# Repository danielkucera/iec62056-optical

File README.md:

# iec62056-optical

Adapter for reading meters with IEC62056 optical interface.

View this project [online](https://kicanvas.org/?github=https%3A%2F%2Fgithub.com%2Fdanielkucera%2Fiec62056-optical%2Ftree%2Fmaster)

You can buy complete adapter in [my shop](https://lectronz.com/products/iec-62056-optical-interface)

# Photos

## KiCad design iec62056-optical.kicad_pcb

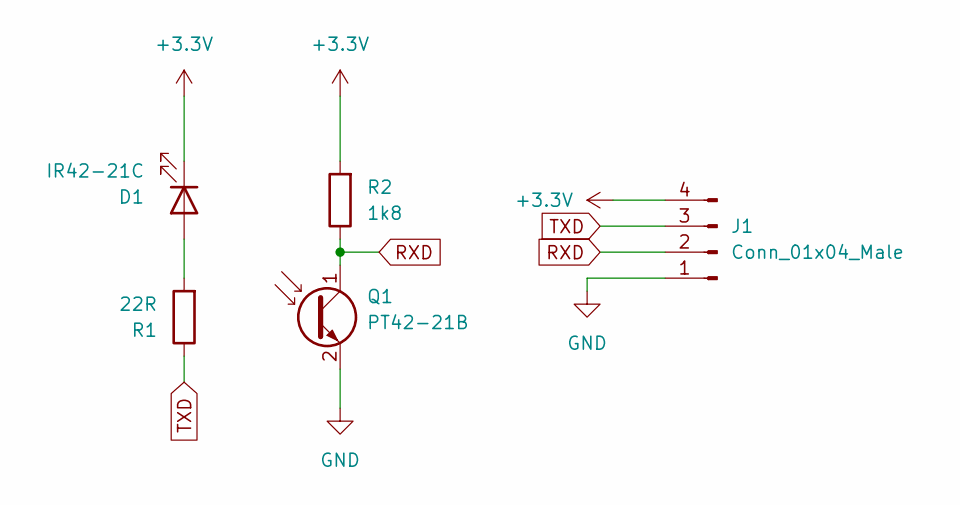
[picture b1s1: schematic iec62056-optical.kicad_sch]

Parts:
D1: IR42-21C; LED_1210_3225Metric; LCSC C131198
J1: Conn_01x04_Male; PinHeader_1x04_P2.54mm_Vertical
Q1: PT42-21B; LED_1210_3225Metric; LCSC C131199
R1: 22R; R_0603_1608Metric; LCSC C23345
R2: 1k8; R_0603_1608Metric; LCSC C4177

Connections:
+3V3: D1.1 (K), J1.4, R2.2
GND: J1.1, Q1.2 (E)
unnamed: D1.2 (A), R1.2
RXD: J1.2, Q1.1 (C), R2.1
TXD: J1.3, R1.1

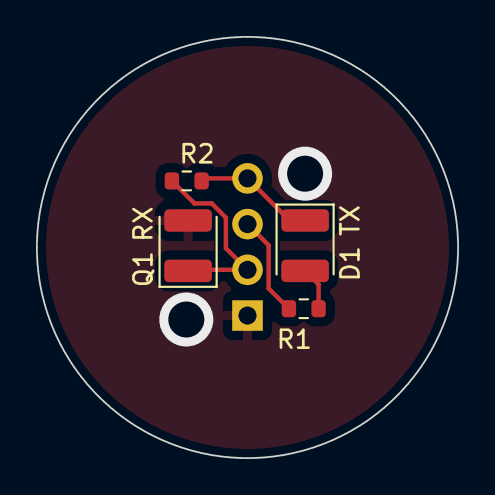
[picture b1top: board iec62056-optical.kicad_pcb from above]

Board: 2 copper layers, 23.4 x 23.4 mm, 5 parts (1 on the bottom side), 5 nets.

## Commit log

2022-01-04 work version
2022-10-11 Backlink to CADLAB.io has been added.
2023-02-28 version 1.0
2023-05-19 added case model
2023-05-19 added images
2023-05-22 oprava orientace diody
